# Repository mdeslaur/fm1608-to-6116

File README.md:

# FM1608 to 6116 ram adapter

This is a small adapter board to use inexpensive DIP FM1608 FRAM memory
chip in games that require a 6116 static ram to save ram contents during
power off so a battery is no longer required.

For example, it can be used in Williams pinball System 11 games, or in
Midway MCR games such as Tron.

A 10k surface mount resistor is required for MCR games.

Gerbers for JLCPCB are located in the gerbers directory.
A PDF of the schematic and a 3d render are located in the Docs directory.

Change history:  
2022-05-17 - 1.0 - Initial version  

To Do:  

Marc Deslauriers

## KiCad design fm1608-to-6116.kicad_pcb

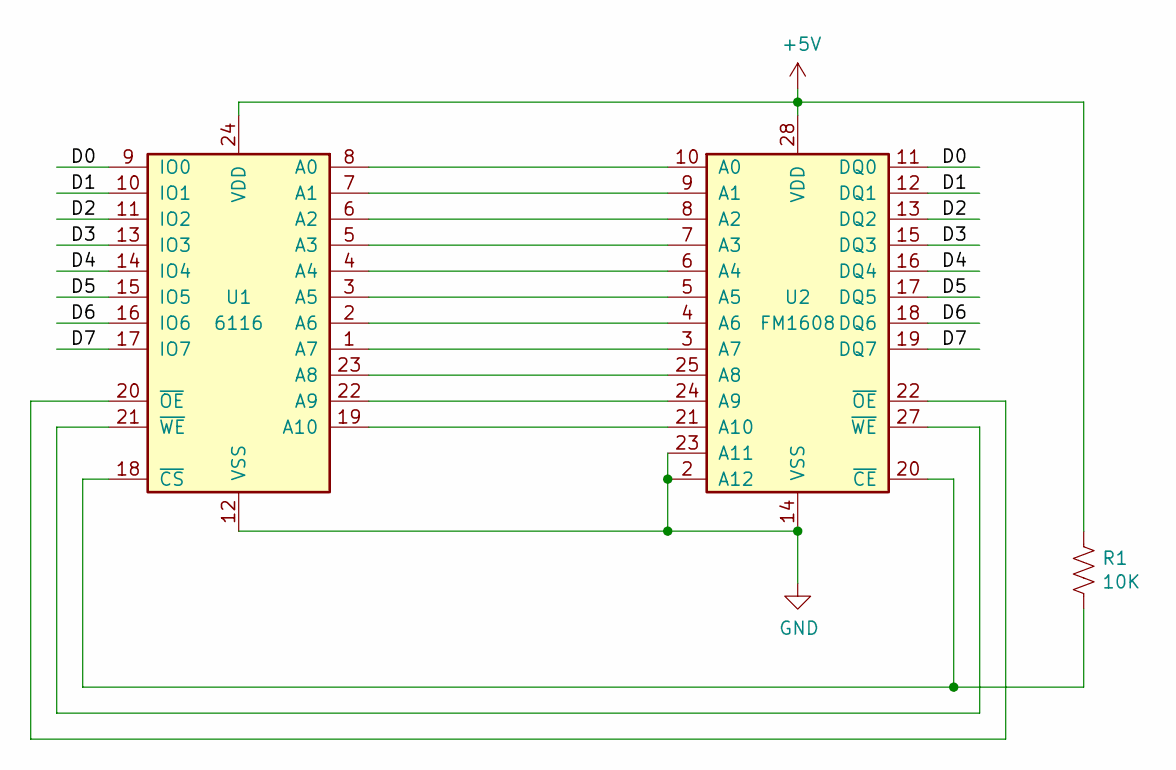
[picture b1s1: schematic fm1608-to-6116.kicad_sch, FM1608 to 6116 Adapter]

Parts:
R1: 10K; R_0805_2012Metric_Pad1.20x1.40mm_HandSolder
U1: 6116; DIP-24_W15.24mm
U2: FM1608; DIP-28_W15.24mm

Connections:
+5V: R1.1, U1.24 (VDD), U2.28 (VDD)
/D0: U1.9 (IO0), U2.11 (DQ0)
/D1: U1.10 (IO1), U2.12 (DQ1)
/D2: U1.11 (IO2), U2.13 (DQ2)
/D3: U1.13 (IO3), U2.15 (DQ3)
/D4: U1.14 (IO4), U2.16 (DQ4)
/D5: U1.15 (IO5), U2.17 (DQ5)
/D6: U1.16 (IO6), U2.18 (DQ6)
/D7: U1.17 (IO7), U2.19 (DQ7)
GND: U1.12 (VSS), U2.2 (A12), U2.14 (VSS), U2.23 (A11)
unnamed: R1.2, U1.18 (~CS), U2.20 (~CE)
unnamed: U1.1 (A7), U2.3 (A7)
unnamed: U1.2 (A6), U2.4 (A6)
unnamed: U1.3 (A5), U2.5 (A5)
unnamed: U1.4 (A4), U2.6 (A4)
unnamed: U1.5 (A3), U2.7 (A3)
unnamed: U1.6 (A2), U2.8 (A2)
unnamed: U1.7 (A1), U2.9 (A1)
unnamed: U1.8 (A0), U2.10 (A0)
unnamed: U1.19 (A10), U2.21 (A10)
unnamed: U1.20 (~OE), U2.22 (~OE)
unnamed: U1.21 (~WE), U2.27 (~WE)
unnamed: U1.22 (A9), U2.24 (A9)
unnamed: U1.23 (A8), U2.25 (A8)

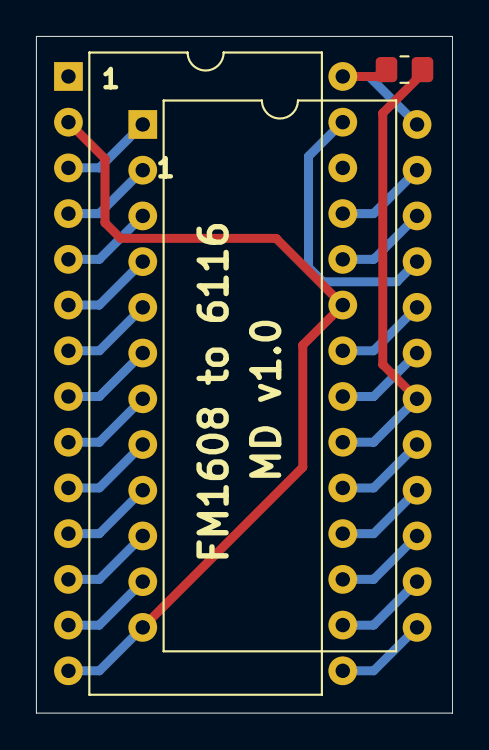
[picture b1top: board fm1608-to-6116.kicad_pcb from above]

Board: 2 copper layers, 23.1 x 37.6 mm, 3 parts (0 on the bottom side), 24 nets.

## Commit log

2024-12-27 Converted to Kicad 8.x
2024-12-29 Updated to kicad 8.x format
2024-12-29 added .gitignore file to ignore backup files
2024-12-29 added schematic pdf and renders to Docs folder
2024-12-29 updated README.md file
